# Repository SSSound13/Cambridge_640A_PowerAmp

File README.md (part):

# Cambridge Audio Azur 640A — новая основная плата

> **Плата тестируется.**

**Русский** · [English](README.en.md) · [Сайт проекта](https://SSSound13.github.io/Cambridge_640A_PowerAmp/)

Последняя ревизия проекта для **Cambridge 640A V1**, на основе заводской схемы AP12707/6 и PCB AP12708/6a. Сохранены топология усилителя и выходные модули Sanken SAP15.

## Статус

[Текущий DRC](doc/v2/routing-review/final-drc.json): нет нарушений по меди, несоединений и расхождений со схемой. Сохраняются замечания к шелкографии и монтажным контурам D2/R107. [Проверка разводки](doc/v2/ROUTING_TOPOLOGY_REVIEW.md). Файлы производства и монтажные карты относятся к предыдущей ревизии.

## Файлы проекта

- [Регулятор громкости: единый проект KiCad](hardware/volume-control/README.md) — сборка ALPS, две редактируемые платы, заводская медь на справочных слоях; механика на согласовании.
- [Перечень деталей — одна таблица BOM](BOM.md) · [скачать Excel](https://github.com/SSSound13/Cambridge_640A_PowerAmp/raw/refs/heads/main/BOM.xlsx).
- [Проект KiCad ZIP](doc/v2/routing-review/Cambridge640A_routing_review.zip) · [открыть KiCad-проект](640A_PowerAmp.kicad_pro). Нужен KiCad 10 или новее.
- [Gerber и сверловка — ZIP для производства](production/Cambridge_640A_PowerAmp_production.zip) · [Параметры изготовления](production/README.md).
- [Четыре слоя и принципы разводки](#все-четыре-слоя-платы) · [все слои PDF](doc/v2/routing-review/routing-review.pdf).
- [Подключение проводов](doc/v2/WIRING.md).
- [Первое включение и настройка](doc/v2/FIRST_POWER_UP_V2.md) · [PDF](doc/v2/FIRST_POWER_UP_V2.pdf).
- [Заводской сервис-мануал AP14676/1](doc/Cambridge_Azur_640A_V1_Service_Manual_AP14676-1.pdf).

## Документы по сборке

- [Пошаговая инструкция ручного монтажа, 13 шагов — PDF](doc/assembly-notes/640A_PowerAmp_v2_assembly_instructions.pdf).
- [Резисторы по номиналам и мощности, карты установки — PDF](doc/assembly-notes/640A_PowerAmp_v2_resistors_by_value.pdf).
- [Порядок сборки, 13 этапов — PDF](doc/640A_PowerAmp_v2_assembly_order.pdf).
- [Монтажные планы и таблица изменений v2 — PDF](doc/640A_PowerAmp_v2_assembly.pdf).
- [Сборка жгутов и подключение платы — PDF](doc/640A_PowerAmp_v2_wiring.pdf).
- [Контакты и цвета проводов текущей платы — PDF](doc/assembly-notes/640A_power_connector_wire_colors.pdf) · [PNG](doc/assembly-notes/640A_power_connector_wire_colors.png).
- [Документы по сборке и их исходные данные](doc/assembly-notes/README.md), [подключение текущей ревизии](doc/v2/WIRING.md), [первое включение и настройка](doc/v2/FIRST_POWER_UP_V2.md) · [PDF](doc/v2/FIRST_POWER_UP_V2.pdf).

Монтажные карты и инструкции ниже относятся к предыдущей ревизии; актуальная плата доступна в KiCad ZIP выше.

## План размещения компонентов

Вид со стороны компонентов, выходные SAP15 — сверху. Позиционные обозначения позволяют найти детали по [BOM](BOM.md). На монтажном виде показаны только контуры и обозначения компонентов, без медных дорожек и полигонов. Это план предыдущей ревизии; актуальное размещение — в KiCad-проекте.

[Открыть векторный план](doc/v2/layer-plans/components.svg) · [Скачать PDF](doc/v2/layer-plans/components.pdf)

## Все четыре слоя платы

На видах разводки показаны только медь, контактные площадки, отверстия и контур платы — без контуров и обозначений компонентов. Каждое изображение можно открыть отдельно в векторном формате. Все четыре слоя показаны сверху, без зеркального отражения.

### 1. Верхний слой — F.Cu

Вид со стороны деталей. Здесь проходят локальные соединения каскадов, часть выходных и силовых цепей. Обозначения деталей вынесены на отдельный план компонентов выше.

Принцип: у одинаковых узлов каналов сохранять одинаковую геометрию, не делать длинных обходов ради удобства автоматического трассировщика. Сигнальные дорожки и силовые соединения имеют разную ширину. Расстановка и трассировка рассматриваются вместе: короткое соединение полезнее, если при этом остаётся понятным путь обратного тока.

[PDF](doc/v2/routing-review/F_Cu.pdf)

### 2. Первый внутренний слой — In1.Cu

Основная задача — распределение **+45 В и −45 В** полигонами. На этом же слое проходят отдельные соединительные дорожки; это не сплошной слой питания без разрывов.

Принцип: подводить питание широкими участками меди и сохранять электрическую связность всех частей заливки. На In1.Cu каждая шина соединяет четыре накопительных конденсатора с двумя диодами выпрямителя. От шин к каналам питание идёт по наружным дорожкам.

По сравнению с заводской односторонней разводкой часть питания перенесена с дорожек и проводов на внутреннюю медь. Это даёт больше свободы для распределения токов и уменьшения общих узких участков. Численного выигрыша по сопротивлению и падению напряжения относительно оригинала для этой версии не измеряли.

[PDF](doc/v2/routing-review/In1_Cu.pdf)

### 3. Второй внутренний слой — In2.Cu

Основная задача — **силовая земля PGND**: возвраты выпрямителя, накопительных конденсаторов, выходных каскадов и акустики. Основная область PGND соединяет все восемь накопительных конденсаторов с CN20.3. Область C79/C80 связана с основной землёй дорожкой на F.Cu. Отдельные дорожки присутствуют и на этом слое; вырезы вокруг них видны на плане.

Принцип: силовые токи не должны использовать случайные участки сигнальной земли как свой возврат. Цепи **PGND, GND, digital и AUX0V** разделены по назначению и соединены через **NT1–NT3** возле общей точки банка конденсаторов.

Звезда земли не является новым изобретением этого проекта: в оригинале также есть организация возвратов проводами. Здесь её реализация перенесена в геометрию платы. Это делает соединения воспроизводимыми и уменьшает зависимость от прокладки отдельных проводов. Снижение фона и взаимного влияния каналов пока не подтверждено измерениями.

[PDF](doc/v2/routing-review/In2_Cu.pdf)

### 4. Нижний слой — B.Cu

**Вид сверху, как и для остальных слоёв.** Здесь находится значительная часть межкомпонентных соединений, в том числе сигнальные, выходные и вспомогательные цепи. Нижняя шелкография содержит обозначения цветов проводов у разъёмов.

Принцип: использовать нижнюю медь совместно с остальными слоями, чтобы обходы не превращались в длинные «лестницы». Переключение между слоями выполняется через существующие металлизированные площадки выводных деталей. **Отдельных переходных отверстий в текущем проекте нет.** Это свойство новой платы, а не доказательство преимущества перед заводской односторонней платой.

[PDF](doc/v2/routing-review/B_Cu.pdf)

[Все четыре слоя одним PDF](doc/v2/routing-review/routing-review.pdf) · [Планы с комментариями, PDF](doc/v2/routing-review/topology-review.pdf) · [Общие правила разводки](#общие-правила-разводки)

## Общие правила разводки

- **Соответствующие узлы каналов разводятся одинаково.** Для 21 пары целых цепей проверено точное совпадение формы, слоя и ширины после сдвига. Общие питания, защита и внешние подключения имеют собственную геометрию. [Проверка топологии всех четырёх слоёв](doc/v2/ROUTING_TOPOLOGY_REVIEW.md).
- **Ширина зависит от тока и слоя.** Приняты 0,5 / 0,8 / 1 / 2 / 3,5 мм. Для силовых путей выходов приняты 2 мм на внешней меди 70 мкм, для измерительных отводов TP — 0,5 мм. Основные трансформаторные дорожки имеют ширину 3,5 мм на внешних слоях. Для одного канала 100 Вт / 4 Ом расчёт даёт 5 А RMS и 7,07 А пикового тока. [Расчёт токов, обоснование ширин и ограничения](doc/v2/ROUTING_CURRENT_REVIEW.md).
- **Короткие пути без лишних изгибов.** Важные участки проверены и переработаны вручную после автоматической трассировки. У новых сегментов прямые направления и углы 45°; отсутствие переходов не должно достигаться ценой чрезмерного обхода.
- **Проверяется весь путь тока.** Учитываются не только прямая дорожка, но и возврат, связь полигонов, сужения у площадок и общая точка земель.
- **Четыре слоя проверяются вместе.** В текущем PCB нет нарушений по меди, несоединений или расхождений со схемой. Остались замечания к шелкографии и монтажным контурам D2/R107; полный DRC не чистый. Проверка файлов не заменяет испытание усилителя.

## Конструктивный результат и обслуживание

**Меньше ручных соединений.** В оригинале применены проволочные перемычки LK — в BOM основной платы указано 19 штук — и соединения WIRE LINK. В новой плате эти связи выполнены медью. Результат: меньше операций пайки перемычек и меньше зависимости от их ручной прокладки.

**Более удобное снятие платы.** В оригинале провода трансформатора и выходов припаяны к клеммам. В текущем проекте используются разъёмы JST VH: CN20/CN21 для вторичных обмоток, CN23/CN24 для выходов. На шелкографии указаны номера контактов и цвета проводов. Соединения можно разъединить без выпаивания проводов.

**Питание и возвраты перенесены на внутренние слои.** Вместо одной рабочей стороны меди с проводами и перемычками используются четыре слоя. Полигоны питания и PGND позволяют задать их геометрию в проекте. Назначение — уменьшить влияние больших токов на сигнальные цепи; результат по шуму пока предстоит проверить.

**Повторяемость каналов.** Для соответствующих узлов заданы общие правила размещения и одинаковые локальные маршруты. Это упрощает сравнение каналов при проверке и ремонте. Улучшение разделения каналов в децибелах не заявляется без измерений.

**Удобнее настройка.** Добавлены TP1–TP6 для измерений падения на эмиттерных резисторах. В заводском порядке измерения выполняются непосредственно на резисторах. Назначение контрольных точек — удобное подключение прибора; они сами по себе не изменяют работу усилителя.

**Расширены посадочные места электролитов:** C13/C47 и C22/C42 — **Ø8 мм, шаг 3,5 мм**; C70/C71/C74/C75 — **Ø10 мм, шаг 5 мм**. C13/C47 остаются неполярными. Это запас под более крупные корпуса выбранных деталей.

**Цена этих изменений:** четырёхслойная плата сложнее и дороже односторонней; внутреннюю медь нельзя осмотреть или исправить так же просто, как наружную. Разъёмы добавляют контактные соединения. Отсутствие отдельных переходов не отменяет требований к качеству металлизации отверстий компонентов.

## Источники и файлы

- [Сервис-мануал Cambridge Azur 640A V1 AP14676/1](doc/Cambridge_Azur_640A_V1_Service_Manual_AP14676-1.pdf): заводская схема, монтажный рисунок основной платы и BOM; список 19 LK — печатная стр. 25.
- [Текущая PCB](640A_PowerAmp.kicad_pcb), [схема](640A_PowerAmp.kicad_sch), [BOM](BOM.md).
- [Проверка текущей геометрии и измерительных точек](doc/v2/validation/current_board.json); [посадки и детали](BOM.md).
- [Контрольная сумма PCB и послойных файлов](doc/v2/layer-plans/source.json). Послойные PDF/SVG соответствуют текущей PCB; исходный экспорт выполнен KiCad 10.0.8. План компонентов и верхняя медь разделены на отдельные виды; их PDF и PNG подготовлены из SVG, происхождение указано в source.json. [Производственный комплект Gerber и сверловки](production/README.md).

## Что изменили относительно заводской платы и зачем

Проект позволяет сохранить Cambridge 640A V1 с его штатными выходными модулями SAP15 и базовой схемотехникой, обновив основную плату и сделав её удобнее для сборки и обслуживания. Переработаны пути питания и обратных токов, соединения и посадки деталей. Электрический результат этих решений предстоит подтвердить испытаниями.

| Узел | Заводская плата AP12708/6a | Текущая ревизия | Для чего изменено |
|---|---|---|---|
| Печатная плата | Один слой меди и проволочные соединения | Четыре слоя; по проекту 70 мкм меди снаружи, 35 мкм внутри; толщина 1,6 мм | Развести сигналы, питание и возвраты токов с меньшим количеством общих участков |
| Перемычки | 19 LK и соединения WIRE LINK | Соединения выполнены медью; межслойные переходы через металлизированные площадки компонентов | Уменьшить число ручных соединений и операций пайки |
| Питание выходных каскадов | Наружные дорожки и провода | Полигоны ±45 В на In1.Cu; ширины соединений выбраны по назначению | Снизить сопротивление силовых путей и их влияние на малосигнальные цепи |
| Земля | Возвраты дорожками и проводами к общей точке | PGND, GND, digital и AUX0V соединяются в звезде NT1–NT3; PGND занимает основную область In2.Cu | Управлять путями обратных токов, уменьшить общие сопротивления и взаимное влияние каналов |
| Разводка каналов | Заводская компоновка | У согласованных узлов одинаковые локальные маршруты | Сделать поведение каналов более повторяемым, упростить сравнение при наладке |
| Подключение трансформатора и выходов | Провода припаяны к клеммам | CN20/CN21 и CN23/CN24 — JST VH с маркировкой контактов и цветов проводов | Снимать плату без выпаивания этих проводов, облегчить сборку жгутов |
| D17–D20, основной мост | 1N5402, 3 А | BY550-400, 5 А, по BOM | Увеличить номинальный запас диодов по току; тепловой режим проверить на собранном аппарате |
| RC-снабберы вторичной обмотки | Отсутствуют | R122/R123 по 47 Ом и C79/C80 по 100 нФ | Подавлять высокочастотный звон; 47 Ом — начальный номинал, окончательный подбор по измерениям |
| R41/R43/R96/R98 | 150 Ом / 0,25 Вт | 150 Ом / 0,5 Вт, огнестойкое fusible-исполнение по BOM | Увеличить запас по рассеиваемой мощности в питании входных каскадов |
| Регулировка тока покоя | Подстроечники R116/R68 по 47 Ом | Добавлены параллельные резисторы R120/R121 по 100 Ом | Ограничить сопротивление регулируемой цепи; 47 Ом ∥ 100 Ом ≈ 32 Ом при исправном подстроечнике. При обрыве его ветви остаётся 100 Ом — это не гарантия безопасного тока при неисправности |
| Измерение тока покоя | На выводах резисторов 0,22 Ом | TP1–TP6 | Удобнее закреплять щупы и отдельно проверять оба плеча каждого канала |
| C18/C39, вход | 10 мкФ, неполярный электролит | 2,2 мкФ / 100 В, плёнка WIMA MKS2 | Убрать входной электролит; проверить итоговую АЧХ после уменьшения ёмкости |
| C17/C41, обратная связь | 100 мкФ NP | 220 мкФ NP | Снизить расчётную частоту полюса этой RC-цепи: при 1 кОм примерно с 1,6 до 0,7 Гц; это не нижняя граница АЧХ всего усилителя |
| C24/C28, цепи Цобеля | 100 нФ | 100 нФ / 250 В MKT; R44/R50 остаются 4,7 Ом / 3 Вт | Использовать выбранные плёночные компоненты с запасом по напряжению, сохранив назначение цепи |
| Посадки электролитов | Компактные заводские корпуса | C13/C47 и C22/C42 — Ø8 мм / шаг 3,5 мм; C70/C71/C74/C75 — Ø10 мм / шаг 5 мм | Разместить более крупные доступные компоненты; C13/C47 остаются неполярными |
| +5 В и стабилизаторы | Линейные 7805/7815/7915 | Сохранены U8=7805, U9=7815, U10=7915; текущий BOM предусматривает изоляционные комплекты | Сохранить штатный способ стабилизации. Эксперимент с TRACO отменён, C81 удалён; снижения нагрева от импульсного модуля в текущей версии нет |
| Выходные модули и защита | SAP15N/SAP15P, штатные цепи защиты | Базовая схемотехника сохранена | Сохранить устройство усилителя и возможность обслуживания по заводскому мануалу |

Внутренние слои также содержат отдельные дорожки и вырезы: это не сплошные идеальные плоскости. Геометрия текущей ревизии отличается от первой изготовленной партии; новые посадки и маршруты не появляются на уже собранной плате после обновления файлов.

## Таблица расчётных улучшений

**Числа не являются измерениями.** Таблица сохраняет инженерное обоснование разделения земель и звезды; её нельзя представлять как подтверждённые характеристики последней ревизии.

Все значения в основной таблице — **мВ на 1 А возмущающего тока**; пары чисел — левый / правый канал.

| Воздействие | Заводская плата, расчёт L / R | Прежняя новая разводка, расчёт L / R | Изменение в модели |
|---|---|---|---|
| Полуволновой ток → опора входа | 0,045 / 0,040 | 0 / 0 | Устранён общий резистивный участок в модели |
| Ток заряда → опора входа | 0,050 / 0,034 | 0 / 0 | Устранён общий резистивный участок в модели |
| Ток развязки выходных каскадов → опора входа | 0,023 / 0,031 | 0 / 0 | Устранён общий резистивный участок в модели |
| Ток фильтров C66/C7 (C43/C33) → опора входа | 11,5 / 21,8 | 0,15 / 0,15 | Примерно в 77 / 145 раз меньше |
| Ток развязки ±15 В → опора входа | 6,9 / 18,7–19,6 | 0,15 / 0,15 | Примерно в 46 / 125–131 раз меньше |
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
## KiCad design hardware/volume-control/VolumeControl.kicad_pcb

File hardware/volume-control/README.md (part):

# Регулятор громкости — единый проект KiCad 10

Откройте **VolumeControl.kicad_pro**. Переносите всю папку вместе с `models/`; отдельный PCB из Downloads теряет относительные ссылки на модели.

| Файл | Назначение |
|---|---|
| VolumeControl.kicad_pcb | Основной вид сборки двух плат, ALPS, штырей и габаритов опор. Только визуализация сборки, не файл для изготовления |
| VolumeControl.kicad_sch | Электрическая схема переходника ALPS |
| ALPS_Adapter.kicad_pcb | Редактируемая верхняя плата, 0,5 мм |
| Repair_Reference.kicad_pcb | Редактируемая нижняя плата 0,5 мм со справочной заводской медью |
| Order_Combined.kicad_pcb | Единая заготовка для заказа: две платы, паз 1 мм, две перемычки по 3 мм |

KiCad связывает проект с одним основным PCB. Две редактируемые платы находятся в этой же папке; открывайте их через «Файл → Открыть» в PCB Editor. В основной сборке нижняя плата представлена 3D-моделью. В 2D файлы VolumeControl и ALPS_Adapter похожи: первый содержит ту же верхнюю плату, а нижняя добавлена в него только как 3D-модель. Общую сборку смотрите через Alt+3. Изменения отдельных плат не обновляют сборку автоматически; sync_mechanical.py обновляет сборку по текущим платам, не меняя их разводку и геометрию. Схема описывает только переходник; электрическая схема ремонтной платы ещё не разработана.

## Совмещённая заготовка для заказа

Откройте **Order_Combined.kicad_pcb**. Две платы собраны в одну механически связанную заготовку **82,7 × 81,376 мм**, обе толщиной **0,5 мм**. Между платами паз **1 × 53,7 мм**, на концах две перемычки по **3 мм**. Перед монтажом деталей перемычки разрезать и зачистить. Электрические цепи между платами в заготовке не соединены.

Файлы изготовителю: [VolumeControl_Combined_0.5mm_Gerbers.zip](production/VolumeControl_Combined_0.5mm_Gerbers.zip). Параметры заказа и ограничения: [production/README.md](production/README.md). Согласуйте с изготовителем толщину 0,5 мм, пять металлизированных полуотверстий и фрезеровку 1 мм.

Заготовка формируется из двух редактируемых плат командой `build_order_board.py` через Python KiCad. После изменений нужно пересоздать её и повторно экспортировать Gerber/сверловку. `Update_Assembly.cmd` обновляет только установленную 3D-сборку, а не производственный ZIP.

## Обновление общего 3D-вида после правок

1. Сохраните изменения в `Repair_Reference.kicad_pcb` и/или `ALPS_Adapter.kicad_pcb`.
2. Закройте окно редактора общей сборки `VolumeControl.kicad_pcb`, чтобы не перезаписать результат старой открытой копией.
3. Запустите двойным щелчком `Update_Assembly.cmd` в этой папке и дождитесь сообщения `Assembly updated`.
4. Заново откройте `VolumeControl.kicad_pcb`, затем 3D-просмотр через Alt+3.

Обновление пересоздаёт общий PCB и модель нижней платы из сохранённых файлов; исходные редактируемые платы не меняет. Несохранённые изменения редактора в сборку не попадут. Изображения в `renders/` — отдельные снимки, команда их не обновляет. Габариты опор берутся из `reference/three-supports.json`: при переносе креплений требуется отдельно согласовать этот файл и обе платы.

## Согласование механики

Передний правый угол адаптера обрезан прямоугольной ступенькой. В проекции на ремонтную плату новый угол совпадает с её углом (60;117,876108) мм. Ширина снятого участка 6,523892 мм, глубина 8,5 мм; глубина выбрана до участка за H2, пользователь согласовал прямоугольную форму. Ось H2 и дорожки обеих плат не менялись. Обновлены общий вид и проекция на User.3. Последние проверки после этой правки: `validation/stepped-adapter-drc.json` и `validation/stepped-repair-drc.json`.

**Актуальные корпуса:** R1/R2 — выводные металлоплёночные 24,9 кОм, 1/8 Вт; стандартное место DIN0204, шаг 7,62 мм, отверстия Ø0,7 мм. R3/R4 — 0 Ом, SMD 1206. Соединения у R1/R2 подстроены под новые площадки; выводные резисторы показаны в общей 3D-сборке. Корпус 3,6 × 1,6 мм принят по библиотечному месту и требует сверки с деталями. Последний DRC: `validation/tht-resistors-drc.json` — ошибок и незавершённых соединений нет, 9 предупреждений остаются.

Ремонтная плата удлинена до заводского выреза: **31 × 81,376 мм**, X=60…91, Y=36,5…117,876108 мм. Это на 8,376 мм длиннее предыдущего контура. Торец совпадает с линией начала выреза по совмещённому рисунку мануала; точность до микрона не подразумевается. H1 и H2 теперь проходят через ремонтную и основную платы, H3 — только через основную. Добавлено стандартное отверстие H_ALPS2 Ø3 мм на прежней оси H2 (63,75;114). Головка Ø4,5 мм и зона без меди Ø5,5 мм помещаются внутри нового контура. Локальные правки пользователя, включая удаление J6, сохранены. J5 перенесён на пересечение нового торца с заводской земляной дорожкой C005: (72,080899;117,876108). Добавлены только два участка земли шириной 1 мм на F.Cu; прежние дорожки сохранены.

Три отверстия Ø3 мм без металлизации, стандартные из KiCad, под измеренные шурупы Ø2,7 мм с головкой Ø4,5 мм: H4 удалена, H2 перенесена пользователем в (63,75;114). Адаптер — 50,7 × 68,2 мм по габариту, с диагональным срезом дальнего левого угла; задний край на 3 мм за двигателем текущей габаритной модели, правый край на 3 мм правее редуктора. J2 перенесён к H2, перед редуктором, в (103;113) мм. Надпись RK27 удалена. Верх адаптера расположен на 8,5 мм выше верха основной платы: чистый зазор над основной платой 8,0 мм, над ремонтной платой толщиной 0,5 мм — 7,5 мм, без учёта клея. В 3D представлены адаптер и ремонтная плата; заводская основная плата не моделируется. Опоры H1/H2 заканчиваются на ремонтной плате, H3 — на условной верхней плоскости заводской платы.

В `Repair_Reference.kicad_pcb`:

- **User.1** — ограниченный векторный рисунок нижней меди из мануала, страница 11: X=55…133,2 мм, Y=31,5…174,4 мм. Снизу оставлено 50 мм от нижнего края наших контуров, сверху и по бокам — 5 мм контекста. Это справочная графика, а не электрическая разводка.
- **User.2** — номера площадок регуляторов и замечания к отверстиям.
- **User.3** — контур верхней платы, проекция сверловки Ø3 мм, головки Ø4,5 мм и зоны без меди Ø5,5 мм.
- **User.4** — заводской контур из мануала, обрезанный до той же области.
- **Edge.Cuts** — текущий контур ремонтной платы.

Для просмотра наложения включите User.1–User.4 и Edge.Cuts; рабочие слои меди можно временно скрыть. Вид соответствует общим координатам PCB, а не зеркальному виду при переворачивании физической платы.

Серый — заводская медь, зелёный — ремонтная плата, синий — переходник, жёлтый — заводской край.

**Под ремонтной платой пользователь полностью удаляет заводскую медь шлифованием.** На рисунке эта область осветлена. Пересечения отверстий со старой медью внутри неё не являются конфликтом; рабочие дорожки ремонтной платы остаются и проверены отдельно.

| Ось | Координаты нижней платы, мм | Проверка |
|---|---|---|
| H1 | 67,5;77,7 | Поднята на 2,8 мм к шестипиновому разъёму; заводская медь под ремонтной платой удаляется |
| H2 | 63,75;114 | Через ремонтную и основную платы; ось не перемещалась |
| H3 | 102;77,7 | Прежняя точка |

Три оси и шесть межплатных контактов совпадают. Удаление пользователем короткого хвоста на F.Cu общей сборки перенесено в исходник адаптера. На ремонтной плате удалён отдельный тупиковый хвост длиной 4,5 мм; трасса у VR4 сдвинута на 0,1 мм, зазор увеличен с 0,20 до 0,30 мм. Остальная ручная разводка сохранена, все дорожки шириной 1 мм.

Актуальные проверки: `validation/final-repair-drc.json`, `validation/final-adapter-drc.json`, `validation/order-combined-drc.json`. Ошибок и несоединённых контактов нет. В общей заготовке остаётся 9 предупреждений о внешних библиотеках и мелкой надписи; посадочные места встроены. Старые отчёты отражают предыдущие ревизии. Совпадение пяти краевых контактов с заводской медью: `reference/edge-solder-alignment.json`.

До изготовления остаётся сверить реальные потенциометры, моторные выводы и корпуса R1/R2. Полная электрическая схема ремонтной платы пока не оформлена; успешный PCB DRC её не заменяет.

## Краевые точки пайки к заводской плате

| Контакт | X; Y, мм | Назначение |
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
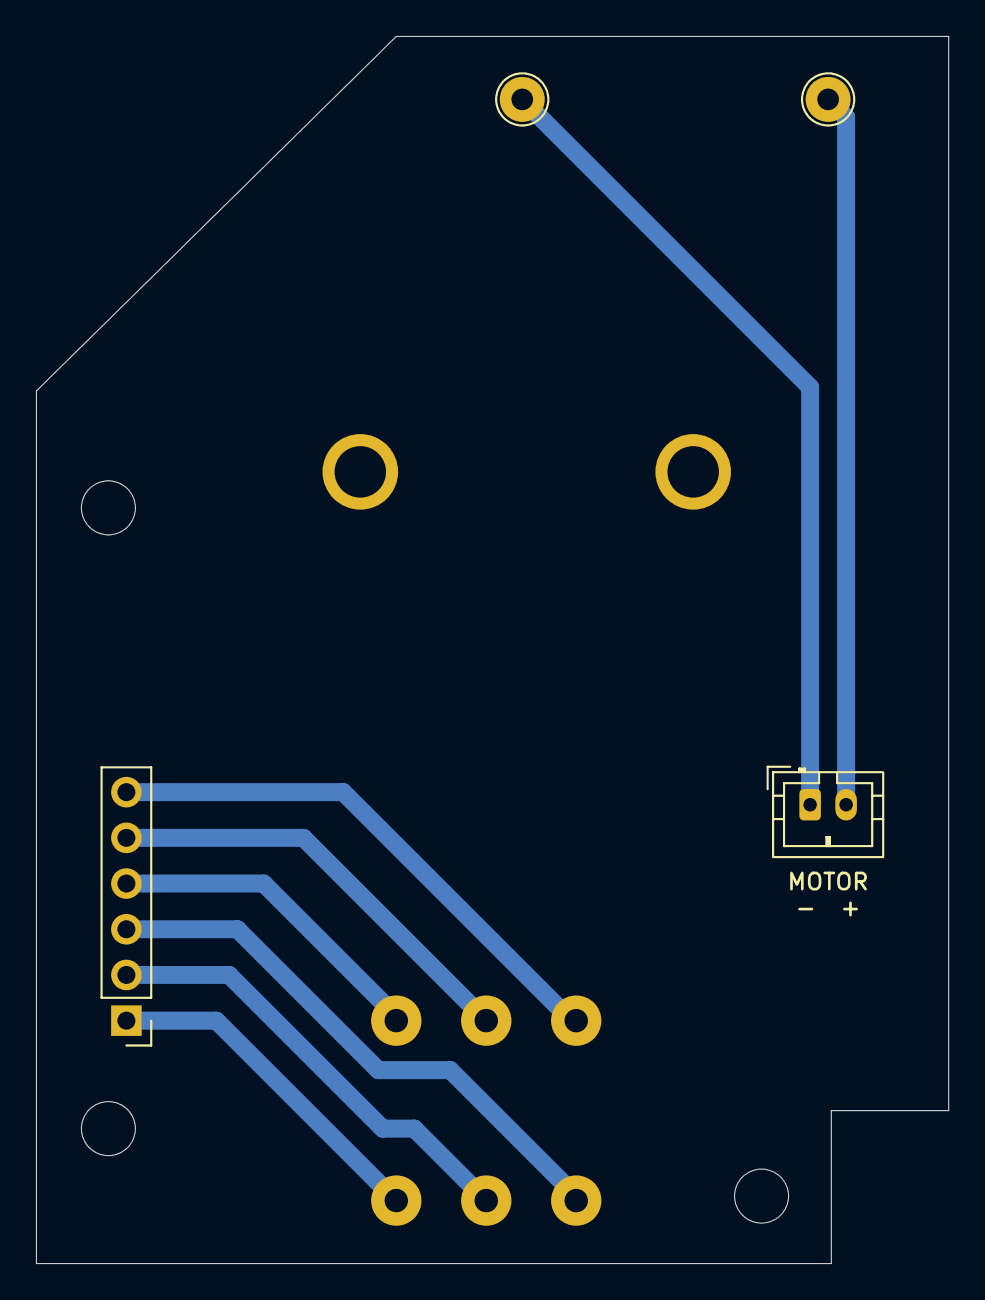
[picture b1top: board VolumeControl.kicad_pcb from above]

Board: 2 copper layers, 50.7 x 68.2 mm, 14 parts (0 on the bottom side), 8 nets.

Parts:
ASSEMBLY_ONLY: (no value)
ASSEMBLY_R1, ASSEMBLY_R2, ASSEMBLY_R3, ASSEMBLY_R4: (no value)
ASSEMBLY_VR4: (no value)
H1, H2, H3: MountingHole_3mm
J1: 1x06 / 2.54 mm; PinHeader_1x06_P2.54mm_Vertical
J2: B2B-PH-K-S; JST_PH_B2B-PH-K_1x02_P2.00mm_Vertical
MP1, MP2: Motor PCB terminal; TestPoint_THTPad_D2.5mm_Drill1.2mm
RV1: RK27112MC / value TBC; RK27112MC

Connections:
/MOTOR_A: J2.1, MP1.1
/MOTOR_B: J2.2, MP2.1
/R1_HIGH: J1.3, RV1.3
/R1_LOW: J1.1, RV1.1
/R1_WIPER: J1.2, RV1.2
/R2_HIGH: J1.6, RV1.6
/R2_LOW: J1.4, RV1.4
/R2_WIPER: J1.5, RV1.5

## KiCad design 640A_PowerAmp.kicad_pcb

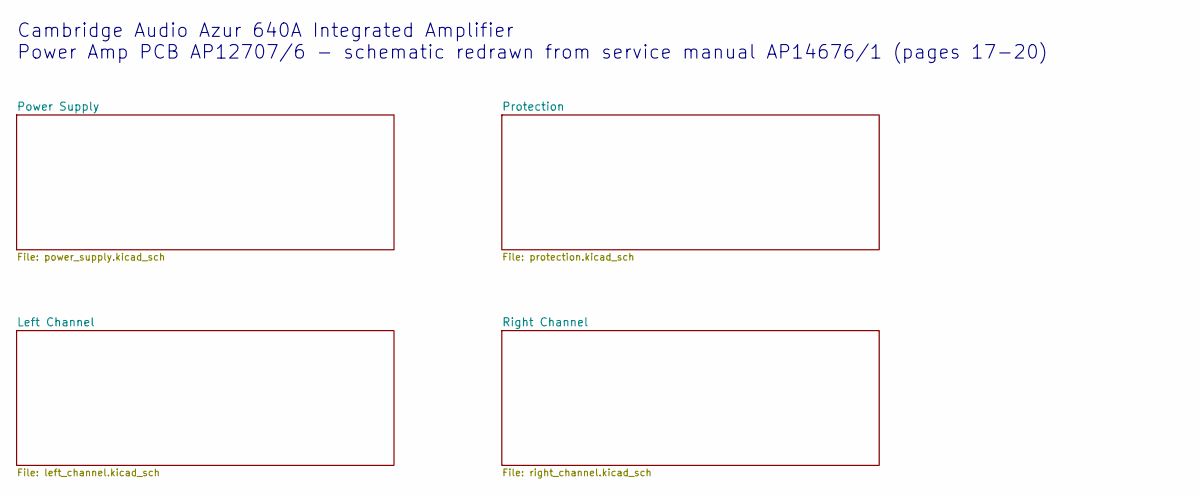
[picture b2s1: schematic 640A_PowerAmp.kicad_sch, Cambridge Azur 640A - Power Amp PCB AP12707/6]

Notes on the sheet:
Cambridge Audio Azur 640A Integrated Amplifier Power Amp PCB AP12707/6 - schematic redrawn from service manual AP14676/1 (pages 17-20)

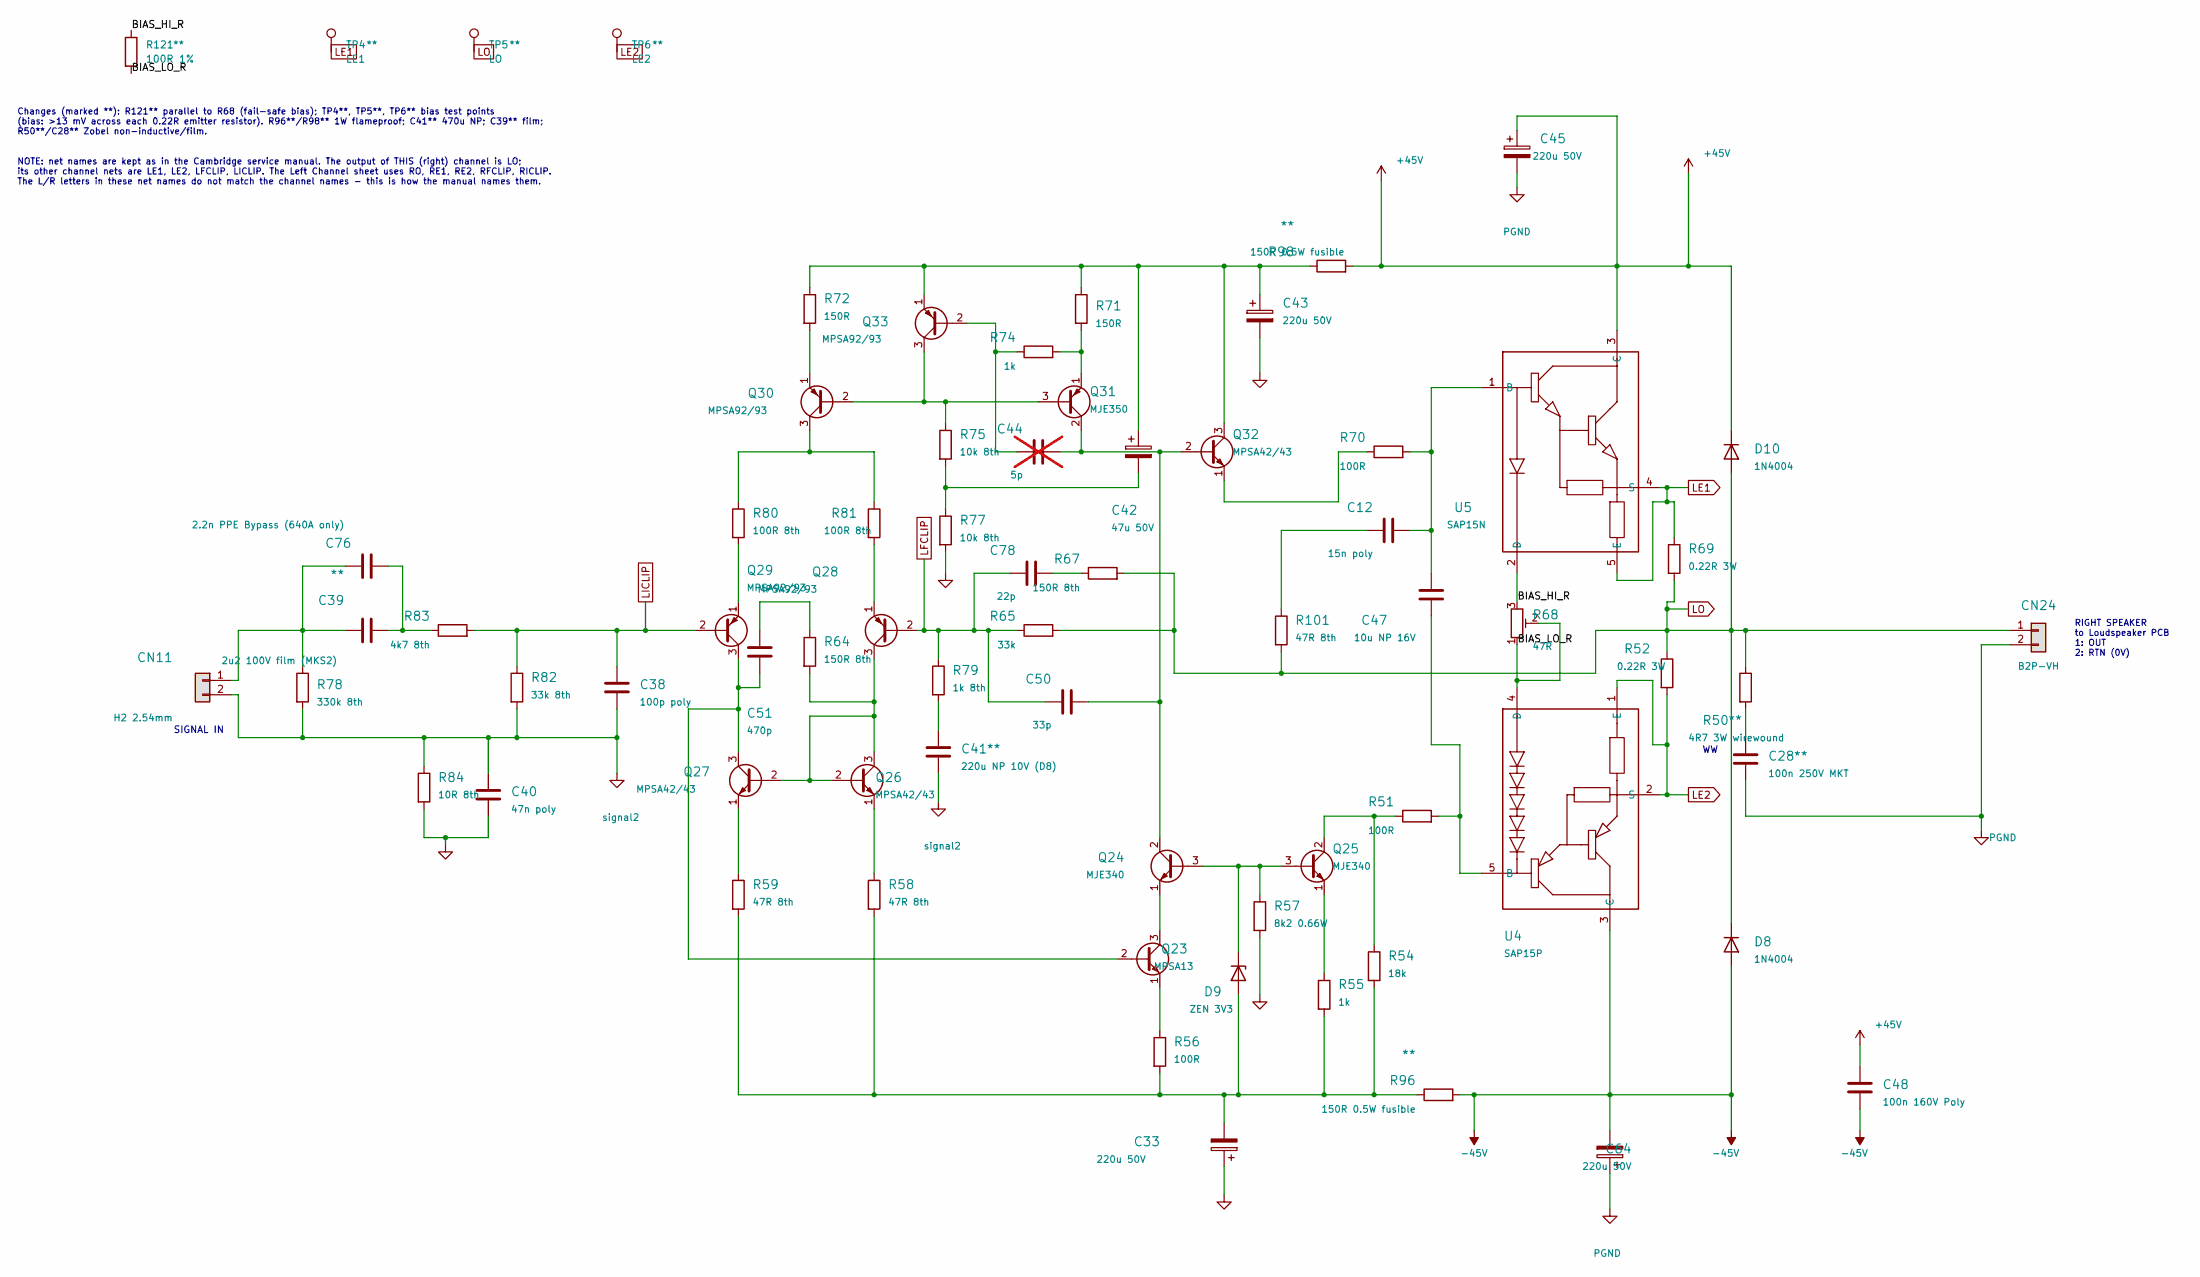
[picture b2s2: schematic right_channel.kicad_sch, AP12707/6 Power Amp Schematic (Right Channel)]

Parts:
C12: 15n poly; C_Rect_L7.2mm_W2.5mm_P5.00mm_FKS2_FKP2_MKS2_MKP2
C28: 100n 250V MKT; C_Rect_L9.0mm_W3.2mm_P7.50mm_MKT; MPN B32560J3104K000
C33, C43, C45, C64: 220u 50V; CP_Radial_D10.0mm_P5.00mm
C38: 100p poly; C_Rect_L7.2mm_W2.5mm_P5.00mm_FKS2_FKP2_MKS2_MKP2
C39: 2u2 100V film (MKS2); C_Rect_L7.2mm_W11.0mm_P5.00mm_FKS2_FKP2_MKS2_MKP2; MPN MKS2D042201N00KO00 (MKS2-2.2U/100-R)
C40: 47n poly; C_Rect_L7.2mm_W2.5mm_P5.00mm_FKS2_FKP2_MKS2_MKP2
C41: 220u NP 10V (D8); C_Radial_D8.0mm_H11.5mm_P3.50mm; MPN ECE-A1AN221U
C42: 47u 50V; CP_Radial_D8.0mm_P3.50mm
C44: 5p; C_Disc_D5.0mm_W2.5mm_P5.00mm; not fitted
C47: 10u NP 16V; C_Radial_D8.0mm_H11.5mm_P3.50mm
C48: 100n 160V Poly; C_Rect_L13.0mm_W4.0mm_P10.00mm_FKS3_FKP3_MKS4
C50: 33p; C_Rect_L7.2mm_W2.5mm_P5.00mm_FKS2_FKP2_MKS2_MKP2
C51: 470p; C_Disc_D5.0mm_W2.5mm_P5.00mm
C76: 2.2n PPE Bypass (640A only); C_Rect_L7.2mm_W2.5mm_P5.00mm_FKS2_FKP2_MKS2_MKP2
C78: 22p; C_Disc_D5.0mm_W2.5mm_P5.00mm
CN11: H2 2.54mm; JST_XH_B2B-XH-A_1x02_P2.50mm_Vertical
CN24: B2P-VH; JST_VH_B2P-VH_1x02_P3.96mm_Vertical; MPN B2P-VH
D8, D10: 1N4004; D_DO-41_SOD81_P8.89mm_Horizontal
D9: ZEN 3V3; D_DO-35_SOD27_P7.62mm_Horizontal
Q23: MPSA13; TO-92_Inline_Wide
Q24, Q25: MJE340; TO-126-3_Vertical
Q26, Q27, Q32: MPSA42/43; TO-92_Inline_Wide
Q28, Q29, Q30, Q33: MPSA92/93; TO-92_Inline_Wide
Q31: MJE350; TO-126-3_Vertical
R50: 4R7 3W wirewound; R_Axial_DIN0516_L15.5mm_D5.0mm_P18.42mm_Horizontal; MPN AC03000004708JAC00
R51, R56, R70: 100R; R_Axial_DIN0207_L6.3mm_D2.5mm_P10.16mm_Horizontal
R52, R69: 0.22R 3W; R_Axial_DIN0516_L15.5mm_D5.0mm_P19.69mm_Horizontal
R54: 18k; R_Axial_DIN0207_L6.3mm_D2.5mm_P10.16mm_Horizontal
R55, R74: 1k; R_Axial_DIN0207_L6.3mm_D2.5mm_P10.16mm_Horizontal
R57: 8k2 0.66W; R_Axial_DIN0309_L9.0mm_D3.2mm_P11.81mm_Horizontal
R58, R59: 47R 8th; R_Axial_DIN0204_L3.6mm_D1.6mm_P7.62mm_Horizontal
R64, R67: 150R 8th; R_Axial_DIN0204_L3.6mm_D1.6mm_P7.62mm_Horizontal
R65: 33k; R_Axial_DIN0207_L6.3mm_D2.5mm_P10.16mm_Horizontal
R68: 47R; Potentiometer_Bourns_3296W_Vertical
R71, R72: 150R; R_Axial_DIN0207_L6.3mm_D2.5mm_P10.16mm_Horizontal
R75, R77: 10k 8th; R_Axial_DIN0204_L3.6mm_D1.6mm_P7.62mm_Horizontal
R78: 330k 8th; R_Axial_DIN0204_L3.6mm_D1.6mm_P7.62mm_Horizontal
R79: 1k 8th; R_Axial_DIN0204_L3.6mm_D1.6mm_P7.62mm_Horizontal
R80, R81: 100R 8th; R_Axial_DIN0204_L3.6mm_D1.6mm_P7.62mm_Horizontal
R82: 33k 8th; R_Axial_DIN0204_L3.6mm_D1.6mm_P7.62mm_Horizontal
R83: 4k7 8th; R_Axial_DIN0204_L3.6mm_D1.6mm_P7.62mm_Horizontal
R84: 10R 8th; R_Axial_DIN0204_L3.6mm_D1.6mm_P7.62mm_Horizontal
R96, R98: 150R 0.5W fusible; R_Axial_DIN0207_L6.3mm_D2.5mm_P10.16mm_Horizontal; MPN FRN50J150R/S
R101: 47R 8th; R_Axial_DIN0204_L3.6mm_D1.6mm_P5.08mm_Horizontal
R121: 100R 1%; R_Axial_DIN0207_L6.3mm_D2.5mm_P10.16mm_Horizontal; MPN MF-25 0.25W 100R 1%
TP4: LE1; TestPoint_THTPad_D2.0mm_Drill1.0mm
TP5: LO; TestPoint_THTPad_D2.0mm_Drill1.0mm
TP6: LE2; TestPoint_THTPad_D2.0mm_Drill1.0mm
U4: SAP15P; TO-3P-5_SAP15_Horizontal
U5: SAP15N; TO-3P-5_SAP15_Horizontal

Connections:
+45V: C45.1, C48.1, D10.1 (K), R98.2, U5.3 (C); also elsewhere on the board
-45V: C48.2, C64.2, D8.2 (A), R96.2, U4.3 (C); also elsewhere on the board
/Right Channel/BIAS_HI_R: R68.3, R121.1, U5.2 (D)
/Right Channel/BIAS_LO_R: R68.1, R68.2, R121.2, U4.4 (D)
GND: C33.1, C40.2, C43.2, R57.2, R77.2, R84.2; also elsewhere on the board
LE1: R69.1, TP4.1 (1_1), U5.4 (S), U5.5 (E); also elsewhere on the board
LE2: R52.2, TP6.1 (1_1), U4.1 (E), U4.2 (S); also elsewhere on the board
LFCLIP: C50.1, C78.1, Q28.2 (B), R65.1, R79.1; also elsewhere on the board
LICLIP: C38.1, Q29.2 (B), R82.1, R83.2; also elsewhere on the board
LO: CN24.1, D8.1 (K), D10.2 (A), R50.1, R52.1, R65.2, R67.2, R69.2, R101.2, TP5.1 (1_1); also elsewhere on the board
unnamed: C12.1, R101.1
unnamed: C28.1, R50.2
unnamed: C39.2, C76.2, R83.1
unnamed: C41.1, R79.2
unnamed: C42.2, R75.2, R77.1
unnamed: C51.1, R64.1
unnamed: C78.2, R67.1
unnamed: C39.1, C76.1, CN11.1, R78.1
unnamed: C33.2, D9.2 (A), R54.2, R55.2, R56.2, R58.2, R59.2, R96.1
unnamed: D9.1 (K), Q24.3 (B), Q25.3 (B), R57.1
unnamed: C51.2, Q23.2 (B), Q27.3 (C), Q29.3 (C)
unnamed: Q23.3 (C), Q24.1 (E)
unnamed: Q23.1 (E), R56.1
unnamed: C44.2, C50.2, Q24.2 (C), Q31.2 (C), Q32.2 (B)
unnamed: Q25.2 (C), R51.1, R54.1
unnamed: Q25.1 (E), R55.1
unnamed: Q26.2 (B), Q26.3 (C), Q27.2 (B), Q28.3 (C), R64.2
unnamed: Q26.1 (E), R58.1
unnamed: Q27.1 (E), R59.1
unnamed: Q28.1 (E), R81.2
unnamed: Q29.1 (E), R80.2
unnamed: Q30.2 (B), Q31.3 (B), Q33.3 (C), R75.1
unnamed: Q30.3 (C), R80.1, R81.1
unnamed: Q30.1 (E), R72.2
unnamed: Q31.1 (E), R71.2, R74.2
unnamed: C42.1, C43.1, Q32.3 (C), Q33.1 (E), R71.1, R72.1, R98.1
unnamed: Q32.1 (E), R70.1
unnamed: C44.1, Q33.2 (B), R74.1
unnamed: C47.2, R51.2, U4.5 (B)
unnamed: C12.2, C47.1, R70.2, U5.1 (B)
PGND: C28.2, C45.2, C64.1, CN24.2; also elsewhere on the board
signal2: C38.2, C40.1, C41.2, CN11.2, R78.2, R82.2, R84.1

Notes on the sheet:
RIGHT SPEAKER to Loudspeaker PCB 1: OUT 2: RTN (0V)
NOTE: net names are kept as in the Cambridge service manual. The output of THIS (right) channel is LO; its other channel nets are LE1, LE2, LFCLIP, LICLIP. The Left Channel sheet uses RO, RE1, RE2, RFCLIP, RICLIP. The L/R letters in these net names do not match the channel names - this is how the m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
SIGNAL IN
Changes (marked **): R121** parallel to R68 (fail-safe bias); TP4**, TP5**, TP6** bias test points (bias: >13 mV across each 0.22R emitter resistor). R96**/R98** 1W flameproof; C41** 470u NP; C39** film; R50**/C28** Zobel non-inductive/film.

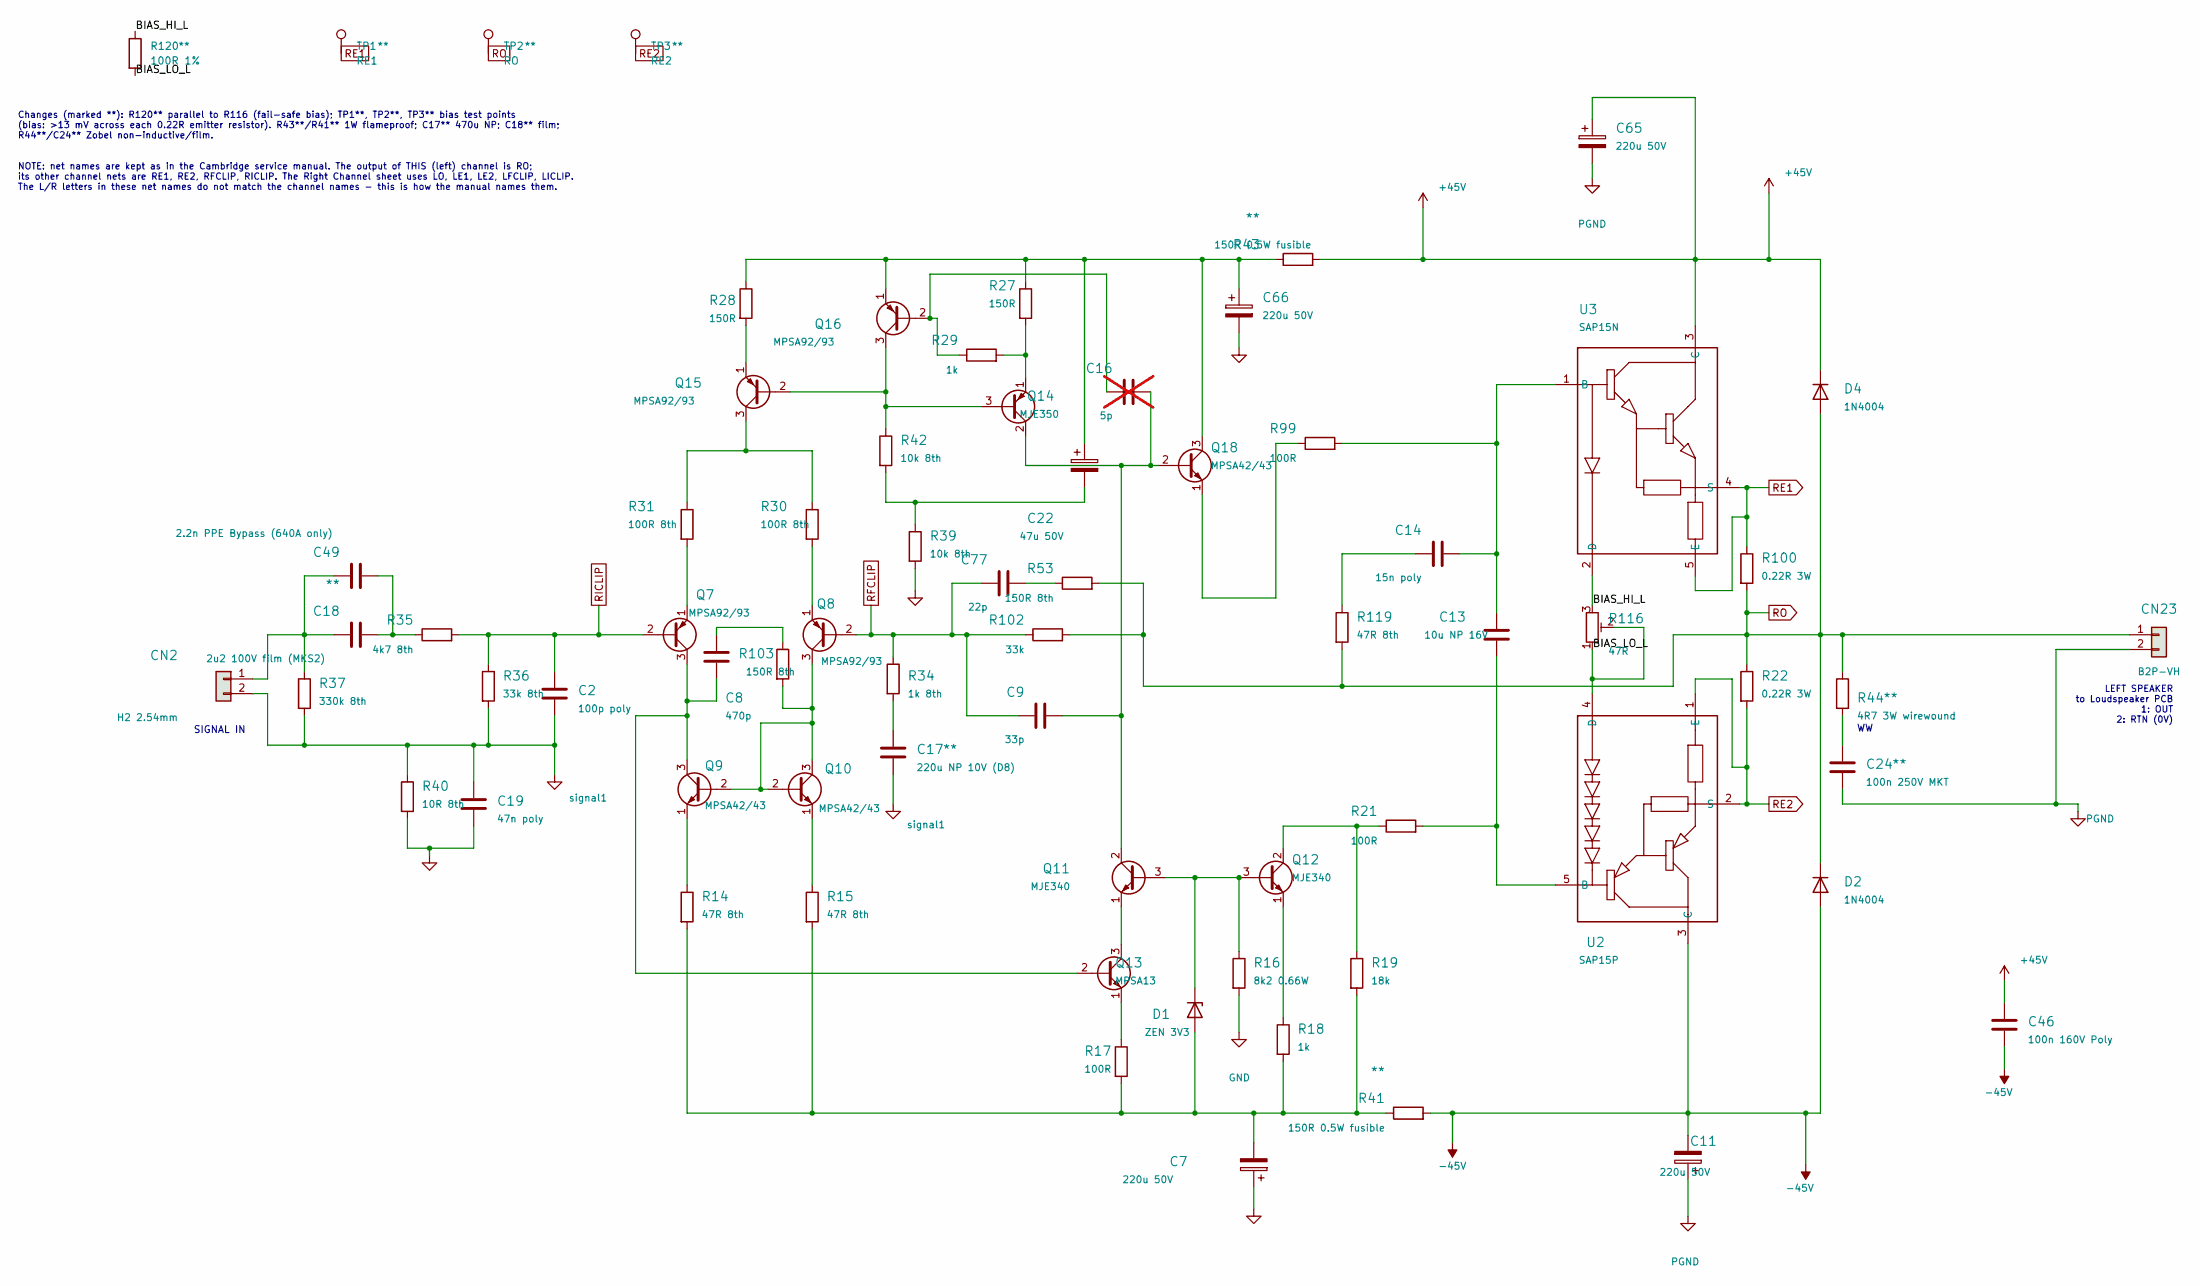
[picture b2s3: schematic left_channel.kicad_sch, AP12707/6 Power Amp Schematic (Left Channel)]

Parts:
C2: 100p poly; C_Rect_L7.2mm_W2.5mm_P5.00mm_FKS2_FKP2_MKS2_MKP2
C7, C11, C65, C66: 220u 50V; CP_Radial_D10.0mm_P5.00mm
C8: 470p; C_Disc_D5.0mm_W2.5mm_P5.00mm
C9: 33p; C_Rect_L7.2mm_W2.5mm_P5.00mm_FKS2_FKP2_MKS2_MKP2
C13: 10u NP 16V; C_Radial_D8.0mm_H11.5mm_P3.50mm
C14: 15n poly; C_Rect_L7.2mm_W2.5mm_P5.00mm_FKS2_FKP2_MKS2_MKP2
C16: 5p; C_Disc_D5.0mm_W2.5mm_P5.00mm; not fitted
C17: 220u NP 10V (D8); C_Radial_D8.0mm_H11.5mm_P3.50mm; MPN ECE-A1AN221U
C18: 2u2 100V film (MKS2); C_Rect_L7.2mm_W11.0mm_P5.00mm_FKS2_FKP2_MKS2_MKP2; MPN MKS2D042201N00KO00 (MKS2-2.2U/100-R)
C19: 47n poly; C_Rect_L7.2mm_W2.5mm_P5.00mm_FKS2_FKP2_MKS2_MKP2
C22: 47u 50V; CP_Radial_D8.0mm_P3.50mm
C24: 100n 250V MKT; C_Rect_L9.0mm_W3.2mm_P7.50mm_MKT; MPN B32560J3104K000
C46: 100n 160V Poly; C_Rect_L13.0mm_W4.0mm_P10.00mm_FKS3_FKP3_MKS4
C49: 2.2n PPE Bypass (640A only); C_Rect_L7.2mm_W2.5mm_P5.00mm_FKS2_FKP2_MKS2_MKP2
C77: 22p; C_Disc_D5.0mm_W2.5mm_P5.00mm
CN2: H2 2.54mm; JST_XH_B2B-XH-A_1x02_P2.50mm_Vertical
CN23: B2P-VH; JST_VH_B2P-VH_1x02_P3.96mm_Vertical; MPN B2P-VH
D1: ZEN 3V3; D_DO-35_SOD27_P7.62mm_Horizontal
D2, D4: 1N4004; D_DO-41_SOD81_P8.89mm_Horizontal
Q7, Q8, Q15, Q16: MPSA92/93; TO-92_Inline_Wide
Q9, Q10, Q18: MPSA42/43; TO-92_Inline_Wide
Q11, Q12: MJE340; TO-126-3_Vertical
Q13: MPSA13; TO-92_Inline_Wide
Q14: MJE350; TO-126-3_Vertical
R14, R15: 47R 8th; R_Axial_DIN0204_L3.6mm_D1.6mm_P7.62mm_Horizontal
R16: 8k2 0.66W; R_Axial_DIN0309_L9.0mm_D3.2mm_P11.81mm_Horizontal
R17, R21, R99: 100R; R_Axial_DIN0207_L6.3mm_D2.5mm_P10.16mm_Horizontal
R18, R29: 1k; R_Axial_DIN0207_L6.3mm_D2.5mm_P10.16mm_Horizontal
R19: 18k; R_Axial_DIN0207_L6.3mm_D2.5mm_P10.16mm_Horizontal
R22, R100: 0.22R 3W; R_Axial_DIN0516_L15.5mm_D5.0mm_P19.69mm_Horizontal
R27, R28: 150R; R_Axial_DIN0207_L6.3mm_D2.5mm_P10.16mm_Horizontal
R30, R31: 100R 8th; R_Axial_DIN0204_L3.6mm_D1.6mm_P7.62mm_Horizontal
R34: 1k 8th; R_Axial_DIN0204_L3.6mm_D1.6mm_P7.62mm_Horizontal
R35: 4k7 8th; R_Axial_DIN0204_L3.6mm_D1.6mm_P7.62mm_Horizontal
R36: 33k 8th; R_Axial_DIN0204_L3.6mm_D1.6mm_P7.62mm_Horizontal
R37: 330k 8th; R_Axial_DIN0204_L3.6mm_D1.6mm_P7.62mm_Horizontal
R39, R42: 10k 8th; R_Axial_DIN0204_L3.6mm_D1.6mm_P7.62mm_Horizontal
R40: 10R 8th; R_Axial_DIN0204_L3.6mm_D1.6mm_P7.62mm_Horizontal
R41, R43: 150R 0.5W fusible; R_Axial_DIN0207_L6.3mm_D2.5mm_P10.16mm_Horizontal; MPN FRN50J150R/S
R44: 4R7 3W wirewound; R_Axial_DIN0516_L15.5mm_D5.0mm_P18.42mm_Horizontal; MPN AC03000004708JAC00
R53, R103: 150R 8th; R_Axial_DIN0204_L3.6mm_D1.6mm_P7.62mm_Horizontal
R102: 33k; R_Axial_DIN0207_L6.3mm_D2.5mm_P10.16mm_Horizontal
R116: 47R; Potentiometer_Bourns_3296W_Vertical
R119: 47R 8th; R_Axial_DIN0204_L3.6mm_D1.6mm_P5.08mm_Horizontal
R120: 100R 1%; R_Axial_DIN0207_L6.3mm_D2.5mm_P10.16mm_Horizontal; MPN MF-25 0.25W 100R 1%
TP1: RE1; TestPoint_THTPad_D2.0mm_Drill1.0mm
TP2: RO; TestPoint_THTPad_D2.0mm_Drill1.0mm
TP3: RE2; TestPoint_THTPad_D2.0mm_Drill1.0mm
U2: SAP15P; TO-3P-5_SAP15_Horizontal
U3: SAP15N; TO-3P-5_SAP15_Horizontal

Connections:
+45V: C46.1, C65.1, D4.1 (K), R43.2, U3.3 (C); also elsewhere on the board
-45V: C11.2, C46.2, D2.2 (A), R41.2, U2.3 (C); also elsewhere on the board
/Left Channel/BIAS_HI_L: R116.3, R120.1, U3.2 (D)
/Left Channel/BIAS_LO_L: R116.1, R116.2, R120.2, U2.4 (D)
GND: C7.1, C19.2, C66.2, R16.2, R39.2, R40.2; also elsewhere on the board
unnamed: C8.1, R103.1
unnamed: C14.1, R119.1
unnamed: C17.1, R34.2
unnamed: C18.2, C49.2, R35.1
unnamed: C22.2, R39.1, R42.2
unnamed: C24.1, R44.2
unnamed: C77.2, R53.1
unnamed: C18.1, C49.1, CN2.1, R37.1
unnamed: C7.2, D1.2 (A), R14.2, R15.2, R17.2, R18.2, R19.2, R41.1
unnamed: D1.1 (K), Q11.3 (B), Q12.3 (B), R16.1
unnamed: Q7.1 (E), R31.2
unnamed: Q8.1 (E), R30.2
unnamed: Q9.1 (E), R14.1
unnamed: Q8.3 (C), Q9.2 (B), Q10.2 (B), Q10.3 (C), R103.2
unnamed: Q10.1 (E), R15.1
unnamed: C9.2, C16.2, Q11.2 (C), Q14.2 (C), Q18.2 (B)
unnamed: Q11.1 (E), Q13.3 (C)
unnamed: Q12.2 (C), R19.1, R21.1
unnamed: Q12.1 (E), R18.1
unnamed: C8.2, Q7.3 (C), Q9.3 (C), Q13.2 (B)
unnamed: Q13.1 (E), R17.1
unnamed: Q14.3 (B), Q15.2 (B), Q16.3 (C), R42.1
unnamed: Q14.1 (E), R27.2, R29.2
unnamed: Q15.3 (C), R30.1, R31.1
unnamed: Q15.1 (E), R28.2
unnamed: C16.1, Q16.2 (B), R29.1
unnamed: C22.1, C66.1, Q16.1 (E), Q18.3 (C), R27.1, R28.1, R43.1
unnamed: Q18.1 (E), R99.1
unnamed: C13.2, R21.2, U2.5 (B)
unnamed: C13.1, C14.2, R99.2, U3.1 (B)
PGND: C11.1, C24.2, C65.2, CN23.2; also elsewhere on the board
RE1: R100.1, TP1.1 (1_1), U3.4 (S), U3.5 (E); also elsewhere on the board
RE2: R22.2, TP3.1 (1_1), U2.1 (E), U2.2 (S); also elsewhere on the board
RFCLIP: C9.1, C77.1, Q8.2 (B), R34.1, R102.1; also elsewhere on the board
RICLIP: C2.1, Q7.2 (B), R35.2, R36.1; also elsewhere on the board
RO: CN23.1, D2.1 (K), D4.2 (A), R22.1, R44.1, R53.2, R100.2, R102.2, R119.2, TP2.1 (1_1); also elsewhere on the board
signal1: C2.2, C17.2, C19.1, CN2.2, R36.2, R37.2, R40.1

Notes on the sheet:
NOTE: net names are kept as in the Cambridge service manual. The output of THIS (left) channel is RO; its other channel nets are RE1, RE2, RFCLIP, RICLIP. The Right Channel sheet uses LO, LE1, LE2, LFCLIP, LICLIP. The L/R letters in these net names do not match the channel names - this is how the m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
LEFT SPEAKER to Loudspeaker PCB 1: OUT 2: RTN (0V)
Changes (marked **): R120** parallel to R116 (fail-safe bias); TP1**, TP2**, TP3** bias test points (bias: >13 mV across each 0.22R emitter resistor). R43**/R41** 1W flameproof; C17** 470u NP; C18** film; R44**/C24** Zobel non-inductive/film.
SIGNAL IN
